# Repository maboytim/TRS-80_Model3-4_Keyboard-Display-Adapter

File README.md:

# TRS-80_Model3-4_Keyboard-Display-Adapter
FPGA based Interface to replace the keyboard and/or CRT display of a TRS-80 Model 3 or 4 with a PS2 keyboard and VGA or HDMI monitor.

### Overview

The adapter can be used to replace the keyboard of a TRS-80 Model 3 or 4 computer with a PS2 keyboard and/or the CRT with a VGA or HDMI monitor.  The adapter uses a low cost Nano-9k FPGA module to simulate the keyboard matrix and to capture and reformat the video signal.

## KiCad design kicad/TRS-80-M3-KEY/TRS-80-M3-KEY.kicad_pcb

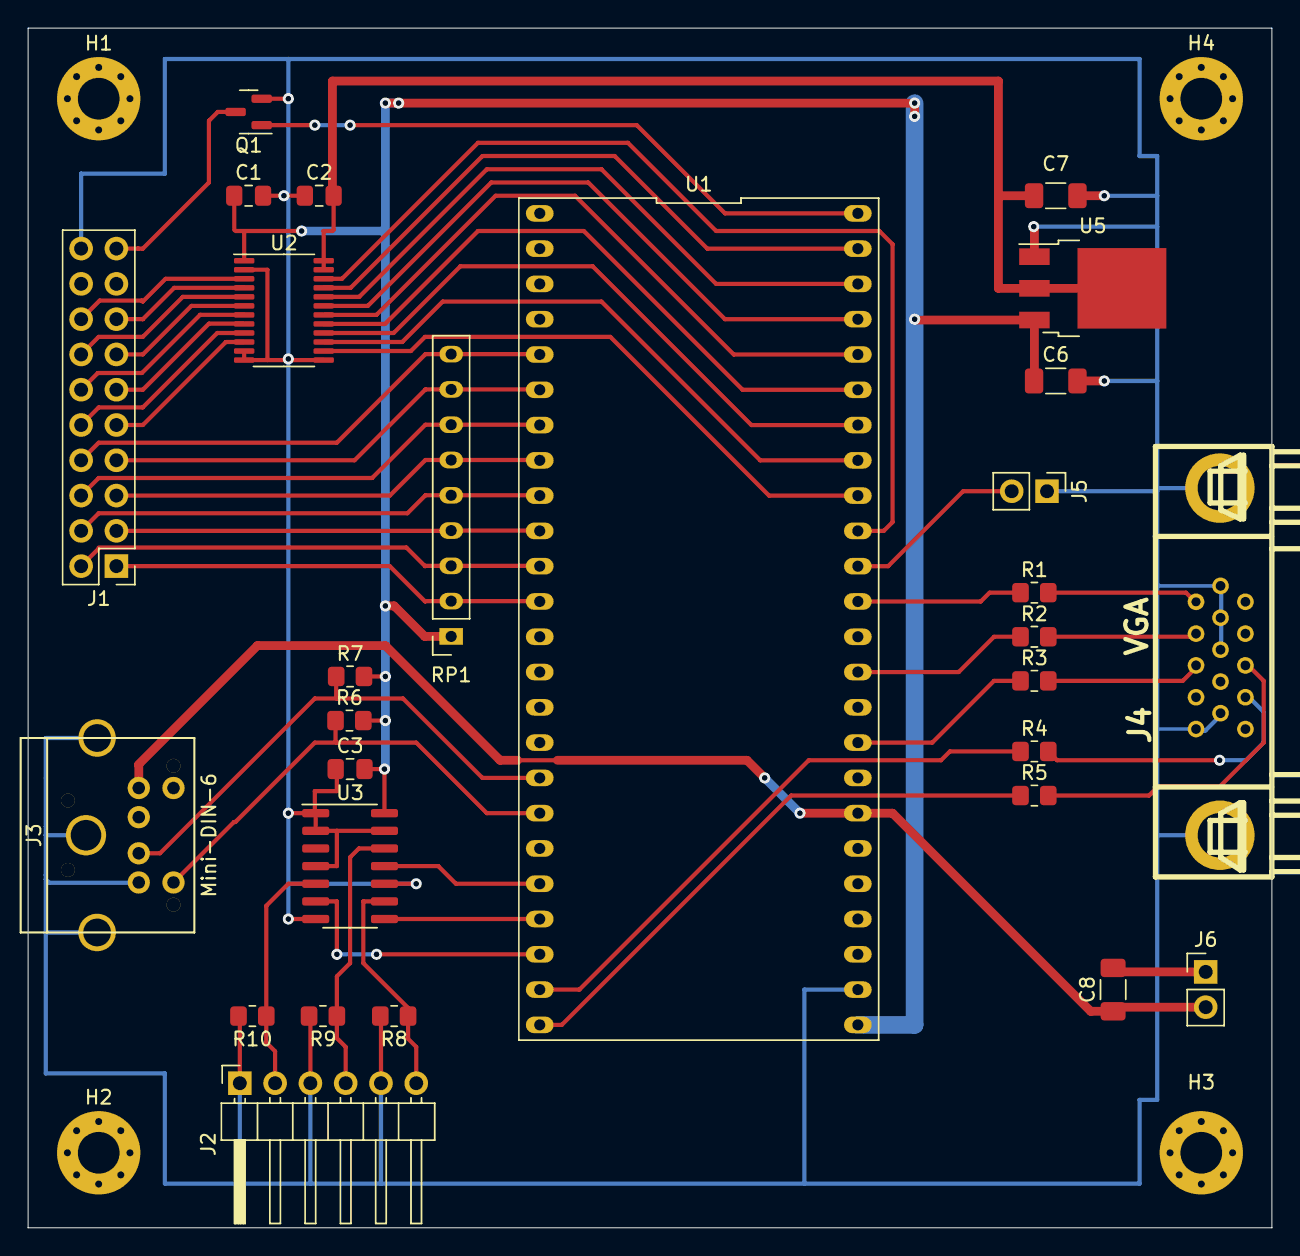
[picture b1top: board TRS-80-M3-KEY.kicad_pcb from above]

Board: 2 copper layers, 89.5 x 86.4 mm, 32 parts (0 on the bottom side), 50 nets.

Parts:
C1, C2, C3: 0.1uF; C_0805_2012Metric_Pad1.18x1.45mm_HandSolder
C6, C7, C8: 10u; C_1206_3216Metric_Pad1.33x1.80mm_HandSolder
H1, H2, H3, H4: MountingHole; MountingHole_3mm_Pad_Via
J1: Keyboard; PinHeader_2x10_P2.54mm_Vertical
J2: Conn_01x06_Male; PinHeader_1x06_P2.54mm_Horizontal
J3: Mini-DIN-6; minidin_6_ps2_pcb_mount
J4: VGA; DB_15F-VGA
J5: Test; PinHeader_1x02_P2.54mm_Vertical
J6: Power; PinHeader_1x02_P2.54mm_Vertical
Q1: 2N2702; SOT-23
R1, R2, R3, R4, R5: 200; R_0805_2012Metric_Pad1.20x1.40mm_HandSolder
R6, R7: 2K; R_0805_2012Metric_Pad1.20x1.40mm_HandSolder
R8, R9, R10: 10k; R_0805_2012Metric_Pad1.20x1.40mm_HandSolder
RP1: R 1kx8; PinSocket_1x09_P2.54mm_Vertical
U1: Tango_Nano_9K; DIP-48_W22.9mm
U2: SN74LVCH8T245; TSSOP-24_4.4x7.8mm_P0.65mm
U3: 74LVC125; SO-14_3.9x8.65mm_P1.27mm
U5: LD1117DT18TR; TO-252-3_TabPin2

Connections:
+1V8: C2.2, C7.1, U2.23 (VCCB), U2.24 (VCCB), U5.2 (VO)
+3V3: C1.1, C3.2, C6.1, R6.2, R7.2, RP1.1, U1.25 (3V3), U2.1 (VCCA), U3.14 (VCC), U5.3 (VI)
+5V: C8.1, J3.4, J6.2, U1.31 (5V)
A0: J1.1, RP1.2, U1.12 (Pad_34)
A1: J1.2, RP1.3, U1.11 (Pad_33)
A2: J1.3, RP1.4, U1.10 (Pad_30)
A3: J1.4, RP1.5, U1.9 (Pad_29)
A4: J1.5, RP1.6, U1.8 (Pad_28)
A5: J1.6, RP1.7, U1.7 (Pad_27)
A6: J1.7, RP1.8, U1.6 (Pad_26)
A7: J1.8, RP1.9, U1.5 (Pad_25)
D0: J1.9, U2.10 (A8)
D1: J1.10, U2.9 (A7)
D2: J1.11, U2.8 (A6)
D3: J1.12, U2.7 (A5)
D4: J1.13, U2.6 (A4)
D5: J1.14, U2.5 (A3)
D6: J1.15, U2.4 (A2)
D7: J1.16, U2.3 (A1)
DD0: U1.40 (Pad_79), U2.14 (B8)
DD1: U1.41 (Pad_80), U2.15 (B7)
DD2: U1.42 (Pad_81), U2.16 (B6)
DD3: U1.43 (Pad_82), U2.17 (B5)
DD4: U1.44 (Pad_83), U2.18 (B4)
DD5: U1.45 (Pad_84), U2.19 (B3)
DD6: U1.46 (Pad_85), U2.20 (B2)
DD7: U1.47 (Pad_86), U2.21 (B1)
DEN_N: U1.39 (Pad_77), U2.22 (OEn)
GND: C1.2, C2.1, C3.1, C6.2, C7.2, C8.2, J1.20, J2.1, J2.3, J2.5, J3.0, J3.3, J4.0 (Case), J4.5, J4.6, J4.7, J4.8, J4.10, J5.1, J6.1, Q1.2 (S), R8.2, R9.2, R10.2, U1.26 (GND), U2.2 (DIR), U2.11 (GND), U2.12 (GND), U2.13 (GND), U3.1, U3.2, U3.4, U3.7 (GND), U3.10, U3.13, U5.1 (GND)
HSYNC: J2.6, R8.1, U3.9
HSYNCX: U1.21 (Pad_56), U3.8
unnamed: J4.1, R1.2
unnamed: J4.2, R2.2
unnamed: J4.3, R3.2
unnamed: J4.13, R5.2
unnamed: J4.14, R4.2
unnamed: J5.2, U1.38 (Pad_76)
PS2_CLK: J3.5, R6.1, U1.18 (Pad_53)
PS2_DTA: J3.1, R7.1, U1.17 (Pad_51)
RST: Q1.1 (G), U1.48 (Pad_63)
RST_N: J1.19, Q1.3 (D)
VGA_BLUE: R3.1, U1.33 (Pad_71)
VGA_GREEN: R2.1, U1.35 (Pad_73)
VGA_HSYNC: R5.1, U1.24 (Pad_69)
VGA_RED: R1.1, U1.37 (Pad_75)
VGA_VSYNC: R4.1, U1.23 (Pad_68)
VIDEO: J2.2, R10.1, U3.5
VIDEOX: U1.22 (Pad_57), U3.6
VSYNC: J2.4, R9.1, U3.12
VSYNCX: U1.20 (Pad_55), U3.11

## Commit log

2022-11-01 Initial commit of all files to the repository
